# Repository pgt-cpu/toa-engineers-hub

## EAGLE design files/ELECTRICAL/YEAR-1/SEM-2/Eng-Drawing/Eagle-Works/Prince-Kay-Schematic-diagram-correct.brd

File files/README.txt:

PUT YOUR PDFs HERE, ARRANGED IN FOLDERS. The site reads the folders by itself.

Example:
  files/Civil/Year 2/Semester 1/CVE 251 Structures/Past Questions/CVE251 2023.pdf
  files/Civil/Year 2/Semester 1/CVE 251 Structures/Lecture Notes/Chapter 1.pdf
  files/Common/Year 1/Semester 1/EMA 151 Engineering Mathematics/Past Questions/EMA151 2022-2023.pdf
  files/Mechanical/Year 4/Timetable.pdf

Only Programme and Year folders are needed. Semester, Course and Type folders are optional.
Use the folder name "Common" for first-year courses shared by every programme.
Add (important) or (verified) to a file name to mark it. Example: 2023 solutions (verified).pdf

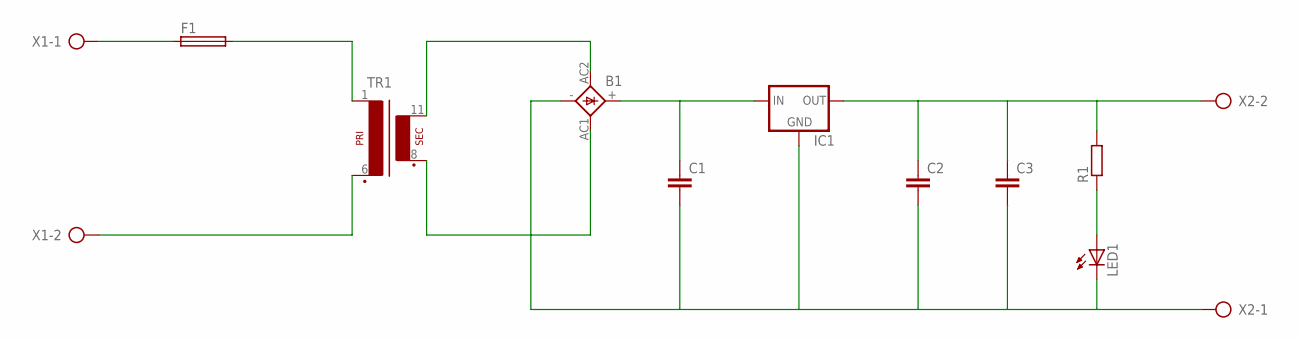
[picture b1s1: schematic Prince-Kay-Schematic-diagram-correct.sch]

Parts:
B1: GBU4; GBU4S
C1, C2, C3: C15/9; C15B9
F1: SHK20L
IC1: 78XXS
LED1: LED5MM
R1: R-EU_0309/10; 0309/10
TR1: EI48-1
X1, X2: AK500/2

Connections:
unnamed: B1.-, C1.2, C2.2, C3.2, IC1.GND, LED1.K (C), X2.1
unnamed: B1.+, C1.1, IC1.IN
unnamed: F1.1A, X1.1
unnamed: F1.2A, TR1.1
unnamed: TR1.6 (P2), X1.2
unnamed: B1.AC2 (AC1), TR1.11 (S4)
unnamed: B1.AC1 (AC2), TR1.8 (S3)
unnamed: C2.1, C3.1, IC1.OUT, R1.2, X2.2
unnamed: LED1.A, R1.1

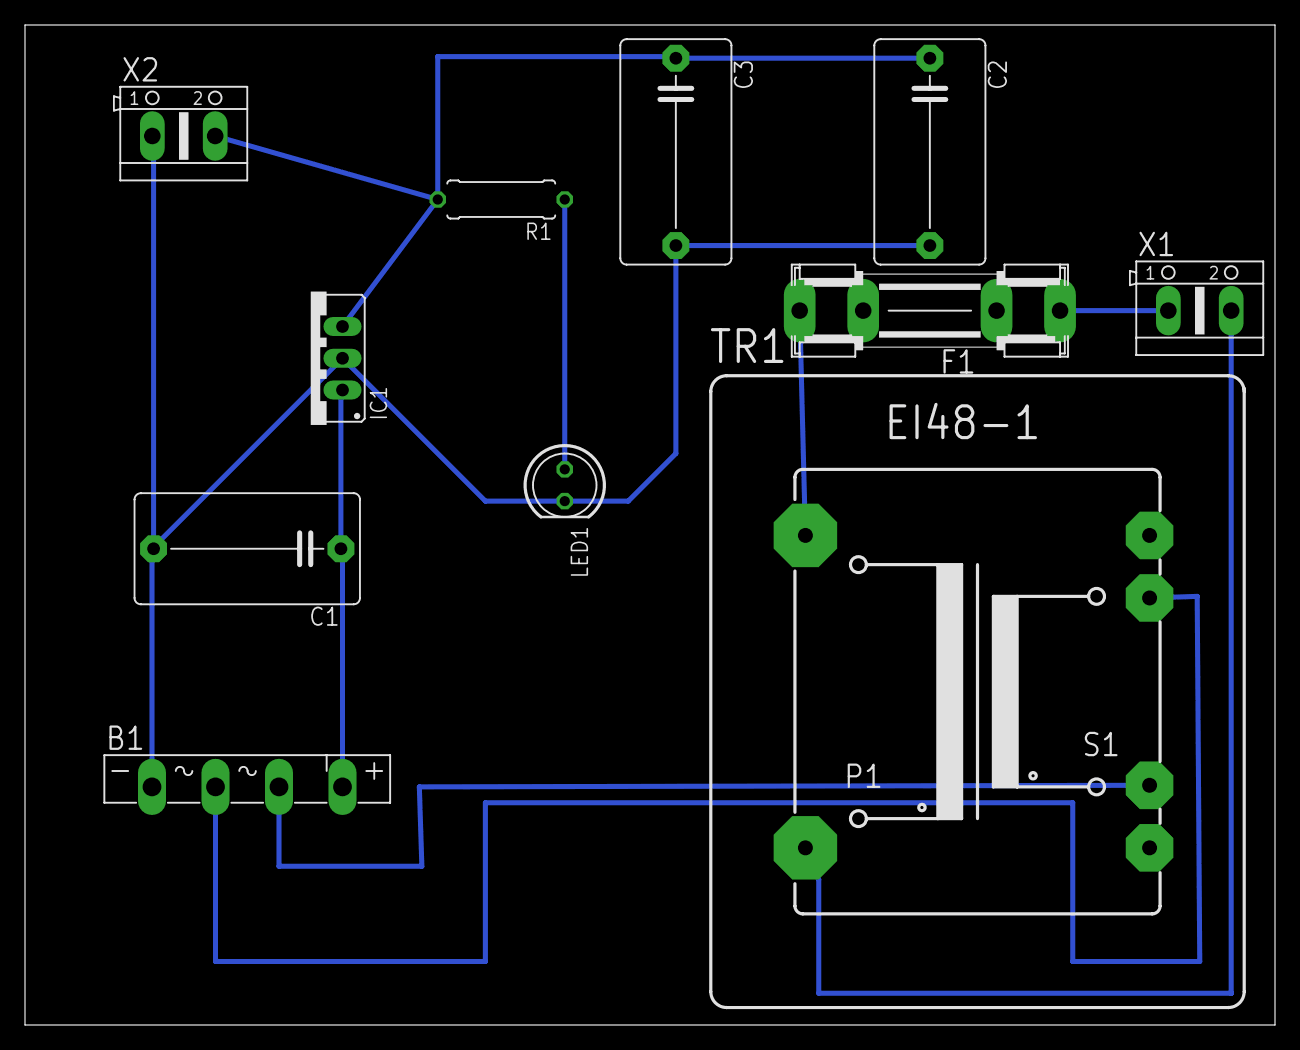
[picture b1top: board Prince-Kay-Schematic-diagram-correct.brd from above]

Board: 2 copper layers, 100.0 x 80.0 mm, 11 parts (0 on the bottom side), 9 nets.
